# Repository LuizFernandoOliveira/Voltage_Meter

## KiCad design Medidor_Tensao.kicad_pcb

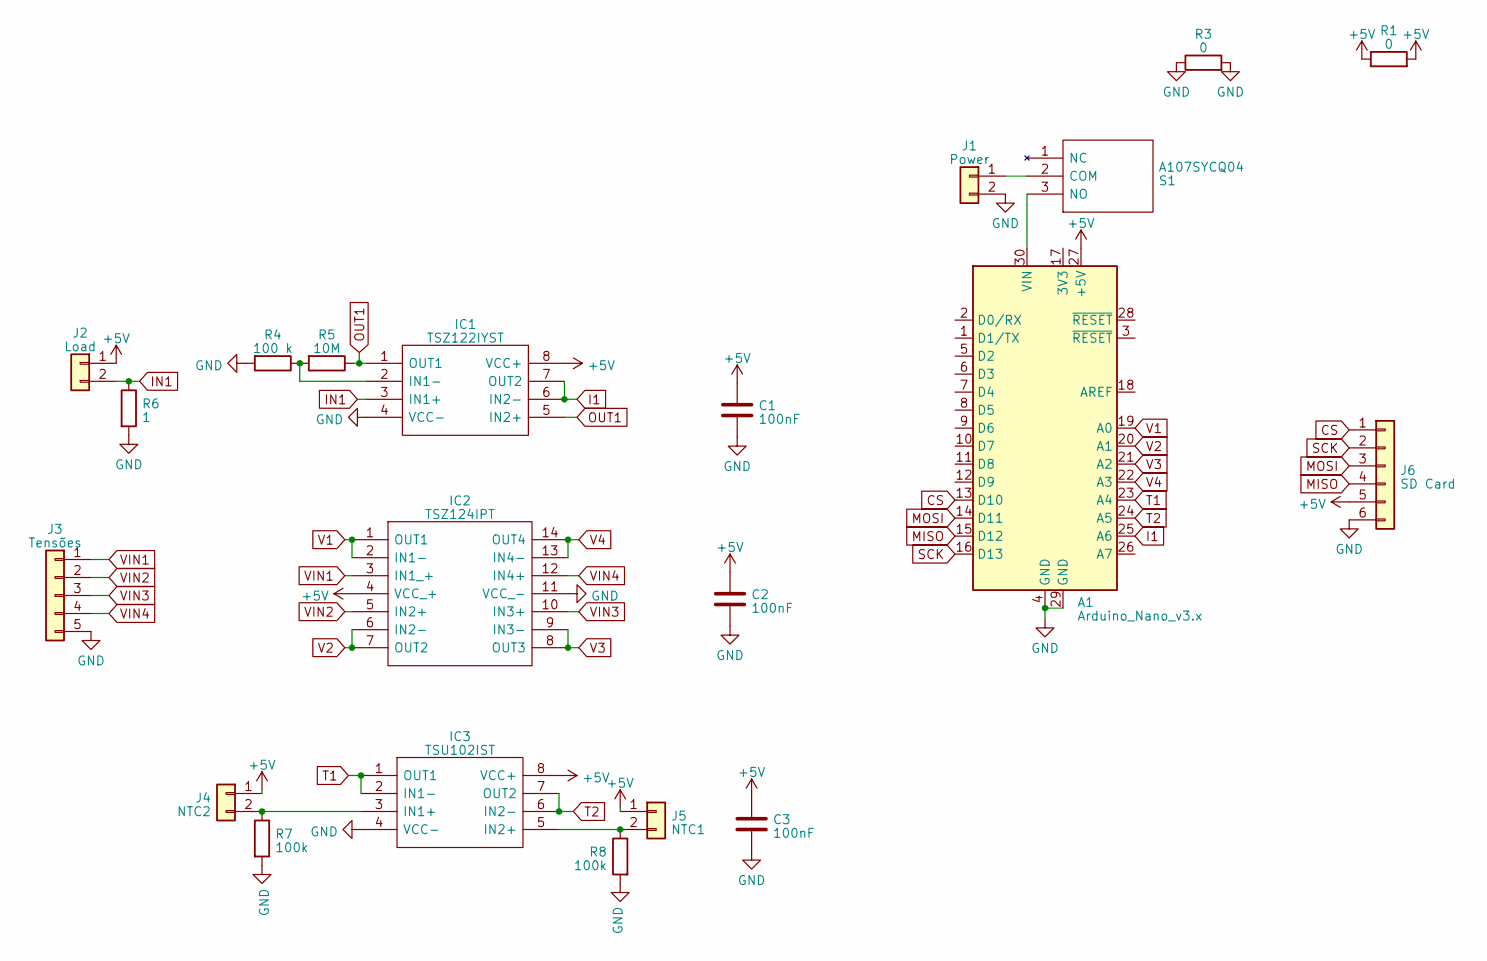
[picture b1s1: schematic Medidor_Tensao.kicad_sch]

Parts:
A1: Arduino_Nano_v3.x; Arduino_Nano
C1, C2, C3: 100nF; C_0805_2012Metric
IC1: TSZ122IYST; SOP65P490X110-8N; Manufacturer_Part_Number TSZ122IYST; Mouser Part Number 511-TSZ122IYST
IC2: TSZ124IPT; SOP65P640X120-14N; Manufacturer_Part_Number TSZ124IPT; Mouser Part Number 511-TSZ124IPT
IC3: TSU102IST; SOP65P490X110-8N; Manufacturer_Part_Number TSU102IST; Mouser Part Number 511-TSU102IST
J1: Power; PinHeader_1x02_P2.54mm_Vertical
J2: Load; PinHeader_1x02_P2.54mm_Vertical
J3: Tensões; PinHeader_1x05_P2.54mm_Vertical
J4: NTC2; PinHeader_1x02_P2.54mm_Vertical
J5: NTC1; PinHeader_1x02_P2.54mm_Vertical
J6: SD Card; PinHeader_1x06_P2.54mm_Vertical
R1, R3: 0; R_1206_3216Metric
R4: 100 k; R_0805_2012Metric
R5: 10M; R_0805_2012Metric
R6: 1; R_0805_2012Metric
R7, R8: 100k; R_0805_2012Metric
S1: A107SYCQ04; Manufacturer_Part_Number A107SYCQ04; Mouser Part Number 506-5-1825137-1

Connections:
+5V: A1.27 (+5V), C1.1, C2.1, C3.1, IC1.8 (VCC+), IC2.4 (VCC_+), IC3.8 (VCC+), J2.1, J4.1, J5.1, J6.5, R1.1, R1.2
CS: A1.13 (D10), J6.1
GND: A1.4 (GND), A1.29 (GND), C1.2, C2.2, C3.2, IC1.4 (VCC-), IC2.11 (VCC_-), IC3.4 (VCC-), J1.2, J3.5, J6.6, R3.1, R3.2, R4.2, R6.2, R7.2, R8.2
I1: A1.25 (A6), IC1.6 (IN2-), IC1.7 (OUT2)
IN1: IC1.3 (IN1+), J2.2, R6.1
MISO: A1.15 (D12), J6.4
MOSI: A1.14 (D11), J6.3
unnamed: A1.30 (VIN), S1.3 (NO)
unnamed: IC1.2 (IN1-), R4.1, R5.2
unnamed: IC3.3 (IN1+), J4.2, R7.1
unnamed: IC3.5 (IN2+), J5.2, R8.1
unnamed: J1.1, S1.2 (COM)
OUT1: IC1.1 (OUT1), IC1.5 (IN2+), R5.1
SCK: A1.16 (D13), J6.2
T1: A1.23 (A4), IC3.1 (OUT1), IC3.2 (IN1-)
T2: A1.24 (A5), IC3.6 (IN2-), IC3.7 (OUT2)
V1: A1.19 (A0), IC2.1 (OUT1), IC2.2 (IN1-)
V2: A1.20 (A1), IC2.6 (IN2-), IC2.7 (OUT2)
V3: A1.21 (A2), IC2.8 (OUT3), IC2.9 (IN3-)
V4: A1.22 (A3), IC2.13 (IN4-), IC2.14 (OUT4)
VIN1: IC2.3 (IN1_+), J3.1
VIN2: IC2.5 (IN2+), J3.2
VIN3: IC2.10 (IN3+), J3.3
VIN4: IC2.12 (IN4+), J3.4

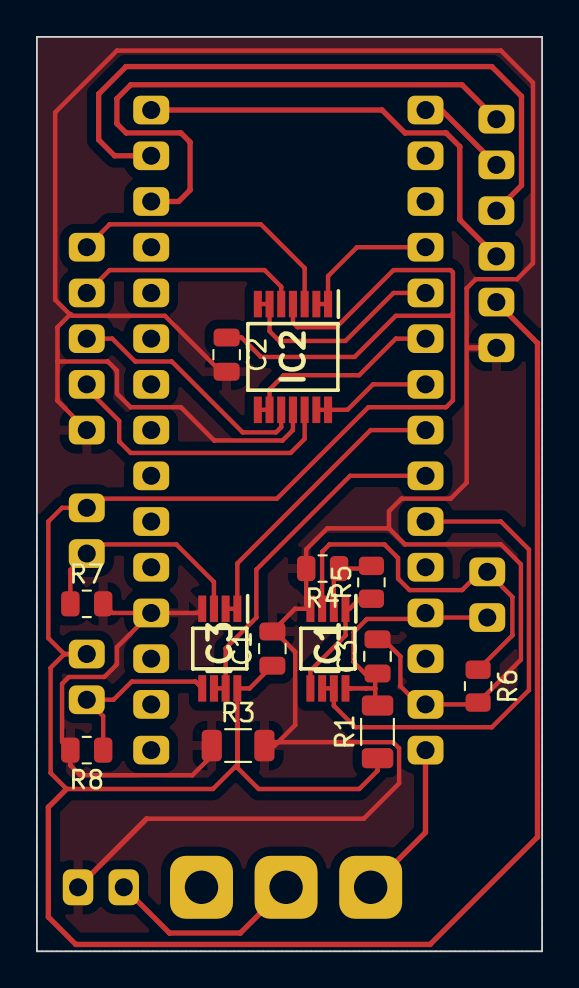
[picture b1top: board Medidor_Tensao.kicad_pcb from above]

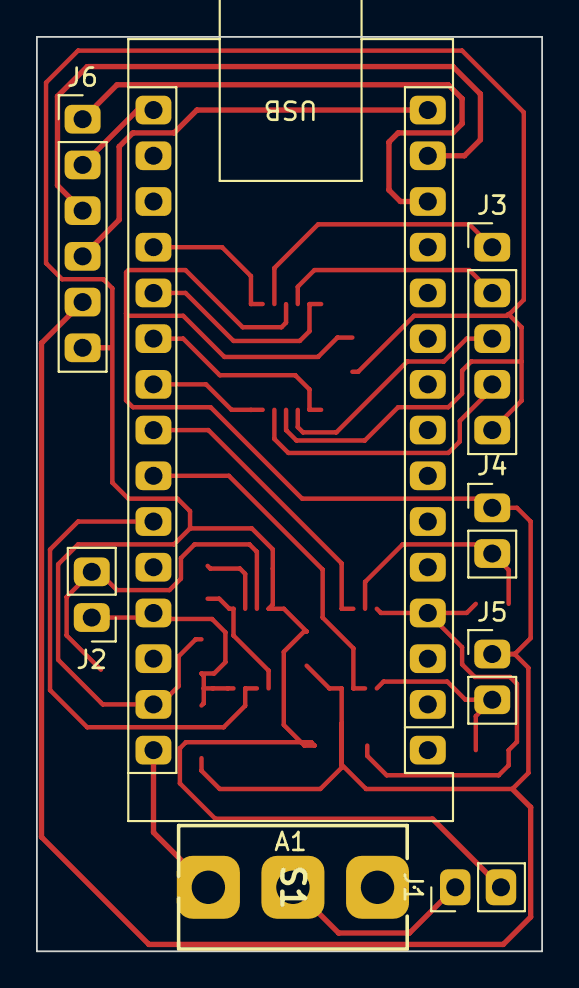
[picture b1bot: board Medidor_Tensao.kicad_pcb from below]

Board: 2 copper layers, 28.1 x 50.8 mm, 21 parts (8 on the bottom side), 24 nets.
